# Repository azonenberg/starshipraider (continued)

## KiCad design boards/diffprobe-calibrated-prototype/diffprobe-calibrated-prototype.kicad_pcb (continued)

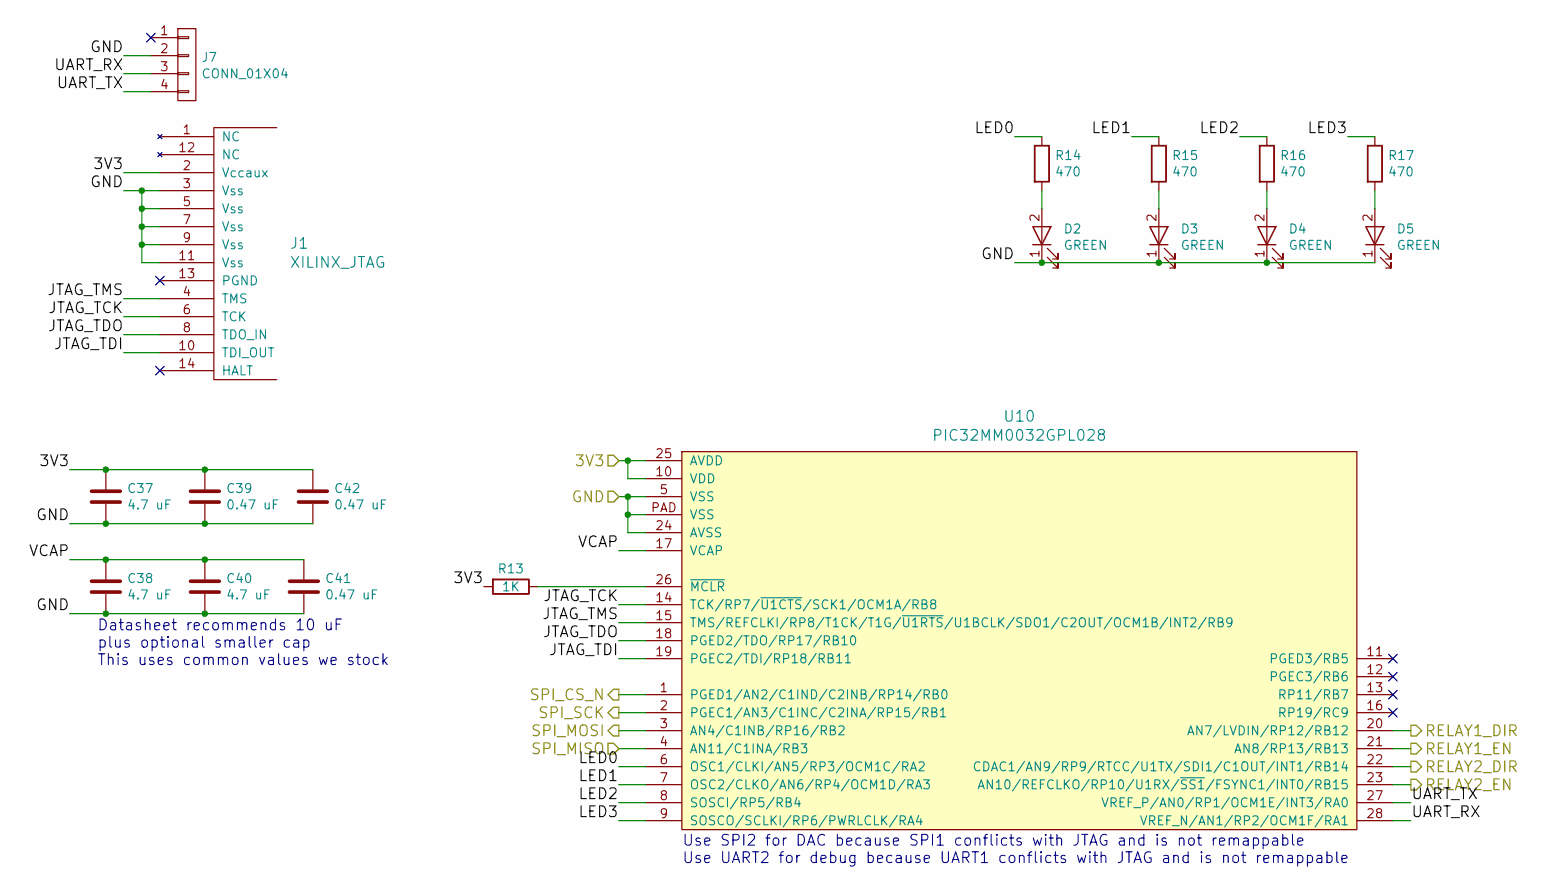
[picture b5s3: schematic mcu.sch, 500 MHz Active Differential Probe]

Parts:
C37, C38, C40: 4.7 uF; EIA_0603_CAP_NOSILK
C39, C41, C42: 0.47 uF; EIA_0402_CAP_NOSILK
D2, D3, D4, D5: GREEN; EIA_0603_LED
J1: XILINX_JTAG; XILINX_JTAG_PTH_MOLEX_0878311420
J7: CONN_01X04; CONN_HEADER_2.54MM_1x4
R13: 1K; EIA_0402_RES_NOSILK
R14, R15, R16, R17: 470; EIA_0402_RES_NOSILK
U10: PIC32MM0032GPL028; QFN_28_0.65MM_6x6MM

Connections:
/3V3: C37.1, C39.1, C42.1, J1.2 (Vccaux), R13.2, U10.10 (VDD), U10.25 (AVDD); also elsewhere on the board
/GND: C37.2, C38.2, C39.2, C40.2, C41.2, C42.2, D2.1 (K), D3.1 (K), D4.1 (K), D5.1 (K), J1.3 (Vss), J1.5 (Vss), J1.7 (Vss), J1.9 (Vss), J1.11 (Vss), J7.2, U10.5 (VSS), U10.24 (AVSS), U10.PAD (VSS); also elsewhere on the board
/Microcontroller/JTAG_TCK: J1.6 (TCK), U10.14 (TCK/RP7/~U1CTS~/SCK1/OCM1A/RB8)
/Microcontroller/JTAG_TDI: J1.10 (TDI_OUT), U10.19 (PGEC2/TDI/RP18/RB11)
/Microcontroller/JTAG_TDO: J1.8 (TDO_IN), U10.18 (PGED2/TDO/RP17/RB10)
/Microcontroller/JTAG_TMS: J1.4 (TMS), U10.15 (TMS/REFCLKI/RP8/T1CK/T1G/~U1RTS~/U1BCLK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)
/Microcontroller/LED0: R14.1, U10.6 (OSC1/CLKI/AN5/RP3/OCM1C/RA2)
/Microcontroller/LED1: R15.1, U10.7 (OSC2/CLKO/AN6/RP4/OCM1D/RA3)
/Microcontroller/LED2: R16.1, U10.8 (SOSCI/RP5/RB4)
/Microcontroller/LED3: R17.1, U10.9 (SOSCO/SCLKI/RP6/PWRLCLK/RA4)
/Microcontroller/RELAY1_DIR: U10.20 (AN7/LVDIN/RP12/RB12); also elsewhere on the board
/Microcontroller/RELAY1_EN: U10.21 (AN8/RP13/RB13); also elsewhere on the board
/Microcontroller/RELAY2_DIR: U10.22 (CDAC1/AN9/RP9/RTCC/U1TX/SDI1/C1OUT/INT1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); also elsewhere on the board
/Microcontroller/RELAY2_EN: U10.23 (AN10/REFCLKO/RP10/U1RX/~SS1~/FSYNC1/INT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); also elsewhere on the board
/Microcontroller/SPI_CS_N: U10.1 (PGED1/AN2/C1IND/C2INB/RP14/RB0); also elsewhere on the board
/Microcontroller/SPI_MISO: U10.4 (AN11/C1INA/RB3); also elsewhere on the board
/Microcontroller/SPI_MOSI: U10.3 (AN4/C1INB/RP16/RB2); also elsewhere on the board
/Microcontroller/SPI_SCK: U10.2 (PGEC1/AN3/C1INC/C2INA/RP15/RB1); also elsewhere on the board
/Microcontroller/UART_RX: J7.3, U10.28 (VREF_N/AN1/RP2/OCM1F/RA1)
/Microcontroller/UART_TX: J7.4, U10.27 (VREF_P/AN0/RP1/OCM1E/INT3/RA0)
/Microcontroller/VCAP: C38.1, C40.1, C41.1, U10.17 (VCAP)
unnamed: D2.2 (A), R14.2
unnamed: D3.2 (A), R15.2
unnamed: D4.2 (A), R16.2
unnamed: D5.2 (A), R17.2
unnamed: R13.1, U10.26 (~MCLR)

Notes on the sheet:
Use SPI2 for DAC because SPI1 conflicts with JTAG and is not remappable Use UART2 for debug because UART1 conflicts with JTAG and is not remappable
Datasheet recommends 10 uF plus optional smaller cap This uses common values we stock

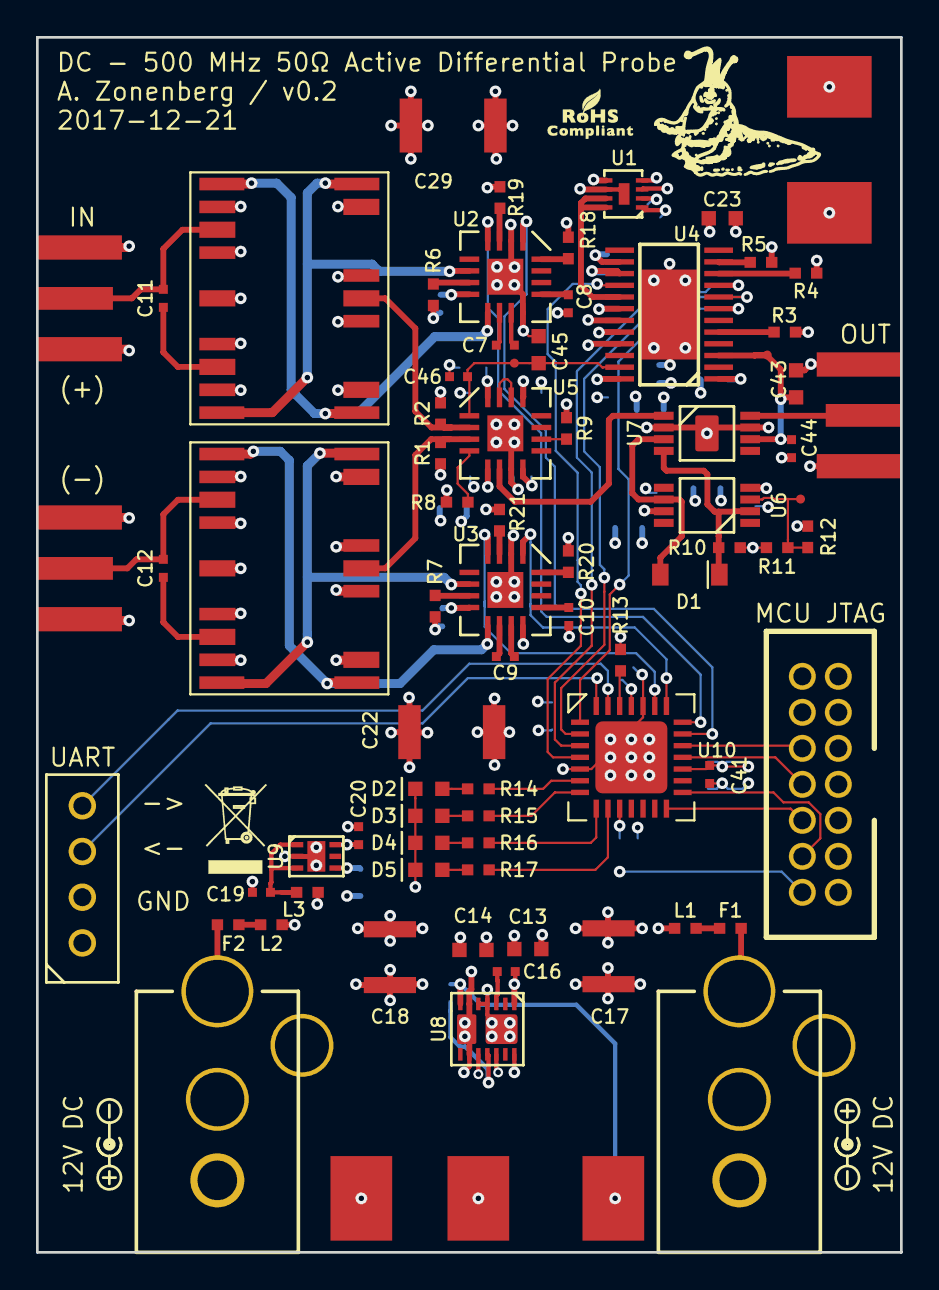
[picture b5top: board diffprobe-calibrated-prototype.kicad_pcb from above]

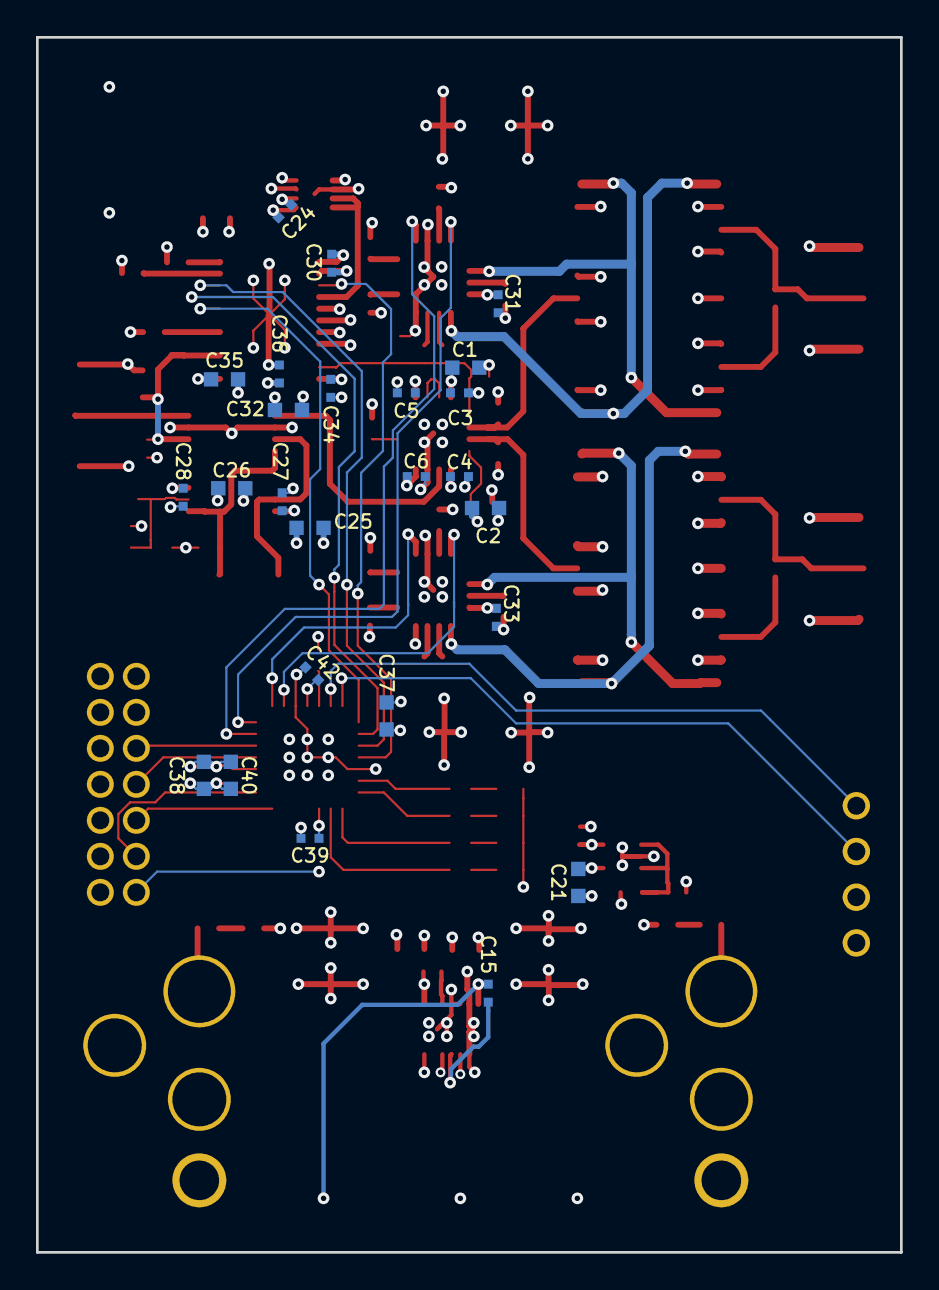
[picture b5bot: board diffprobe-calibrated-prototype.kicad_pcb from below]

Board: 4 copper layers, 48.0 x 67.5 mm, 104 parts (25 on the bottom side), 74 nets.

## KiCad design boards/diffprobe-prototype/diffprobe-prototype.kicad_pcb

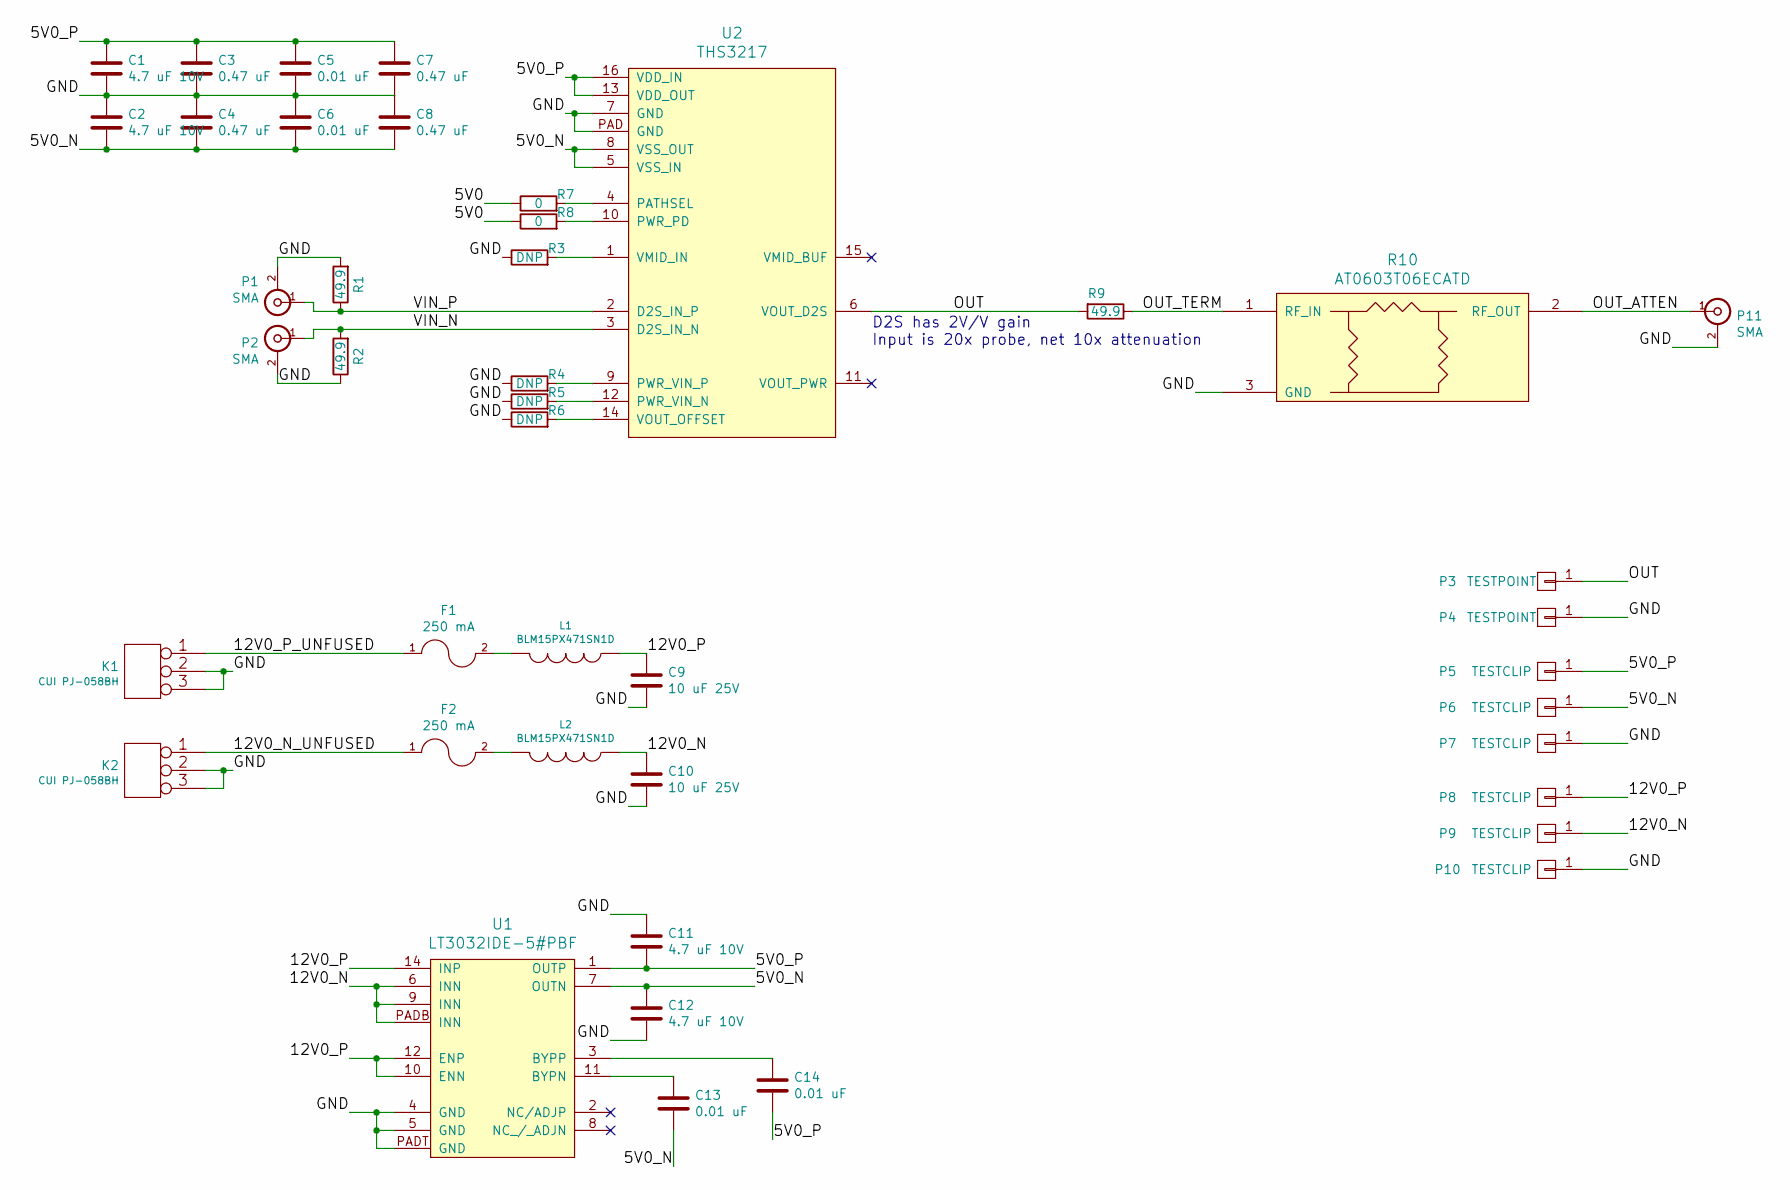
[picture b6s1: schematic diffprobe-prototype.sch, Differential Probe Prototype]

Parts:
C1, C2, C11, C12: 4.7 uF 10V; EIA_0805_CAP_NOSILK
C3, C4, C7, C8: 0.47 uF; EIA_0402_CAP_NOSILK
C5, C6, C13, C14: 0.01 uF; EIA_0402_CAP_NOSILK
C9, C10: 10 uF 25V; EIA_1210_CAP_NOSILK
F1, F2: 250 mA; EIA_0402_RES_NOSILK
K1, K2: CUI PJ-058BH; CONN_CUI_PJ-058BH_HIPWR_BARREL_NOSLOT
L1, L2: BLM15PX471SN1D; EIA_0402_RES_NOSILK
P1, P2, P11: SMA; CONN_SMA_EDGE_SAMTEC_SMA_J_P_H_ST_EM1
P3, P4: TESTPOINT; TESTPOINT_BARETRACE_328UM
P5, P6, P7, P8, P9, P10: TESTCLIP; TESTPOINT_SMT_KEYSTONE_5016
R1, R2, R9: 49.9; EIA_0402_RES_NOSILK
R3, R4, R5, R6: DNP; EIA_0402_RES_NOSILK
R7, R8: 0; EIA_0402_RES_NOSILK
R10: AT0603T06ECATD
U1: LT3032IDE-5#PBF
U2: THS3217

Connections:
/5V0_N: C2.2, C4.2, C6.2, C8.2, C12.1, C13.2, P6.1, U1.7 (OUTN), U2.5 (VSS_IN), U2.8 (VSS_OUT)
/12V0_N: C10.1, L2.1, P9.1, U1.6 (INN), U1.9 (INN), U1.PADB (INN)
/12V0_N_UNFUSED: F2.1, K2.1
/12V0_P: C9.1, L1.1, P8.1, U1.10 (ENN), U1.12 (ENP), U1.14 (INP)
/12V0_P_UNFUSED: F1.1, K1.1
/GND: C1.2, C2.1, C3.2, C4.1, C5.2, C6.1, C7.2, C8.1, C9.2, C10.2, C11.1, C12.2, K1.2 (PM), K1.3, K2.2 (PM), K2.3, P1.2 (Ext), P2.2 (Ext), P4.1, P7.1, P10.1, P11.2 (Ext), R1.2, R2.1, R3.1, R4.1, R5.1, R6.1, R10.3 (GND), U1.4 (GND), U1.5 (GND), U1.PADT (GND), U2.7 (GND), U2.PAD (GND)
/OUT: P3.1, R9.2, U2.6 (VOUT_D2S)
/OUT_ATTEN: P11.1 (In), R10.2 (RF_OUT)
/OUT_TERM: R9.1, R10.1 (RF_IN)
/VIN_N: P2.1 (In), R2.2, U2.3 (D2S_IN_N)
/VIN_P: P1.1 (In), R1.1, U2.2 (D2S_IN_P)
unnamed: C13.1, U1.11 (BYPN)
unnamed: C14.1, U1.3 (BYPP)
unnamed: F1.2, L1.2
unnamed: F2.2, L2.2
unnamed: R3.2, U2.1 (VMID_IN)
unnamed: R4.2, U2.9 (PWR_VIN_P)
unnamed: R5.2, U2.12 (PWR_VIN_N)
unnamed: R6.2, U2.14 (VOUT_OFFSET)
unnamed: R7.2, U2.4 (PATHSEL)
unnamed: R8.2, U2.10 (PWR_PD)

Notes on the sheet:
D2S has 2V/V gain Input is 20x probe, net 10x attenuation

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
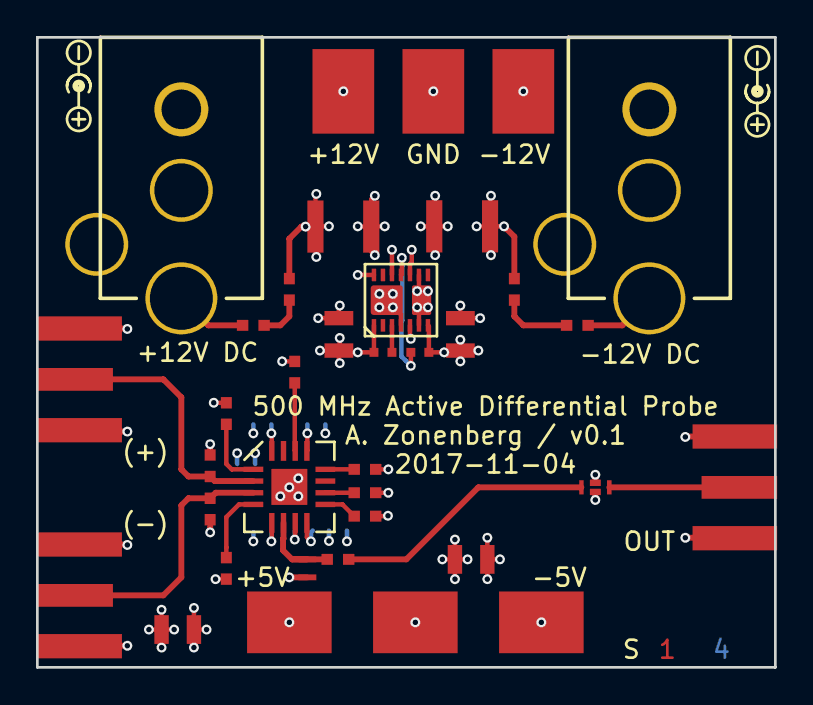
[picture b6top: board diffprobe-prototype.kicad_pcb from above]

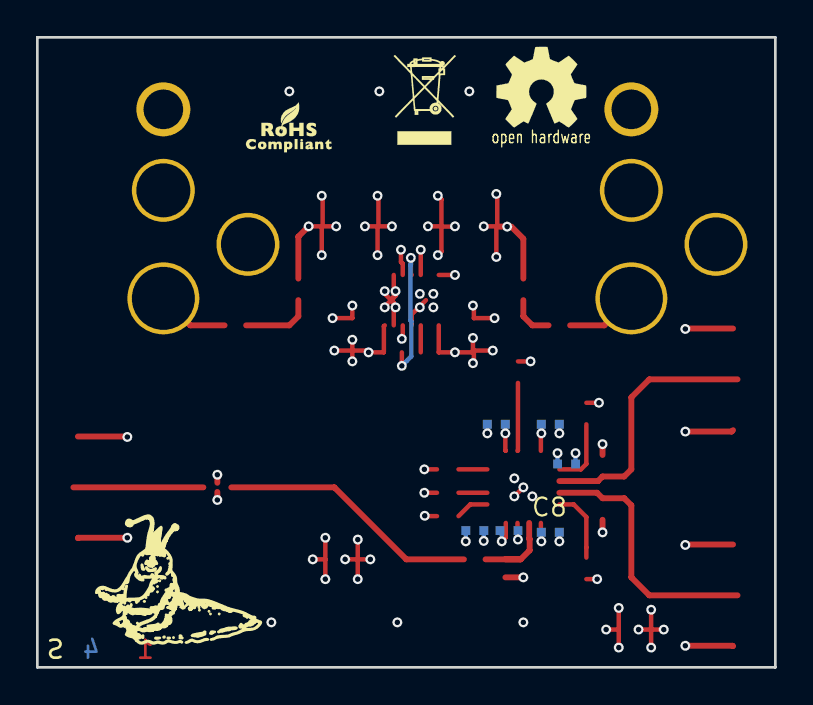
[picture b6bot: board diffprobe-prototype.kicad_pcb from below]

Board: 4 copper layers, 41.0 x 35.0 mm, 43 parts (6 on the bottom side), 22 nets.

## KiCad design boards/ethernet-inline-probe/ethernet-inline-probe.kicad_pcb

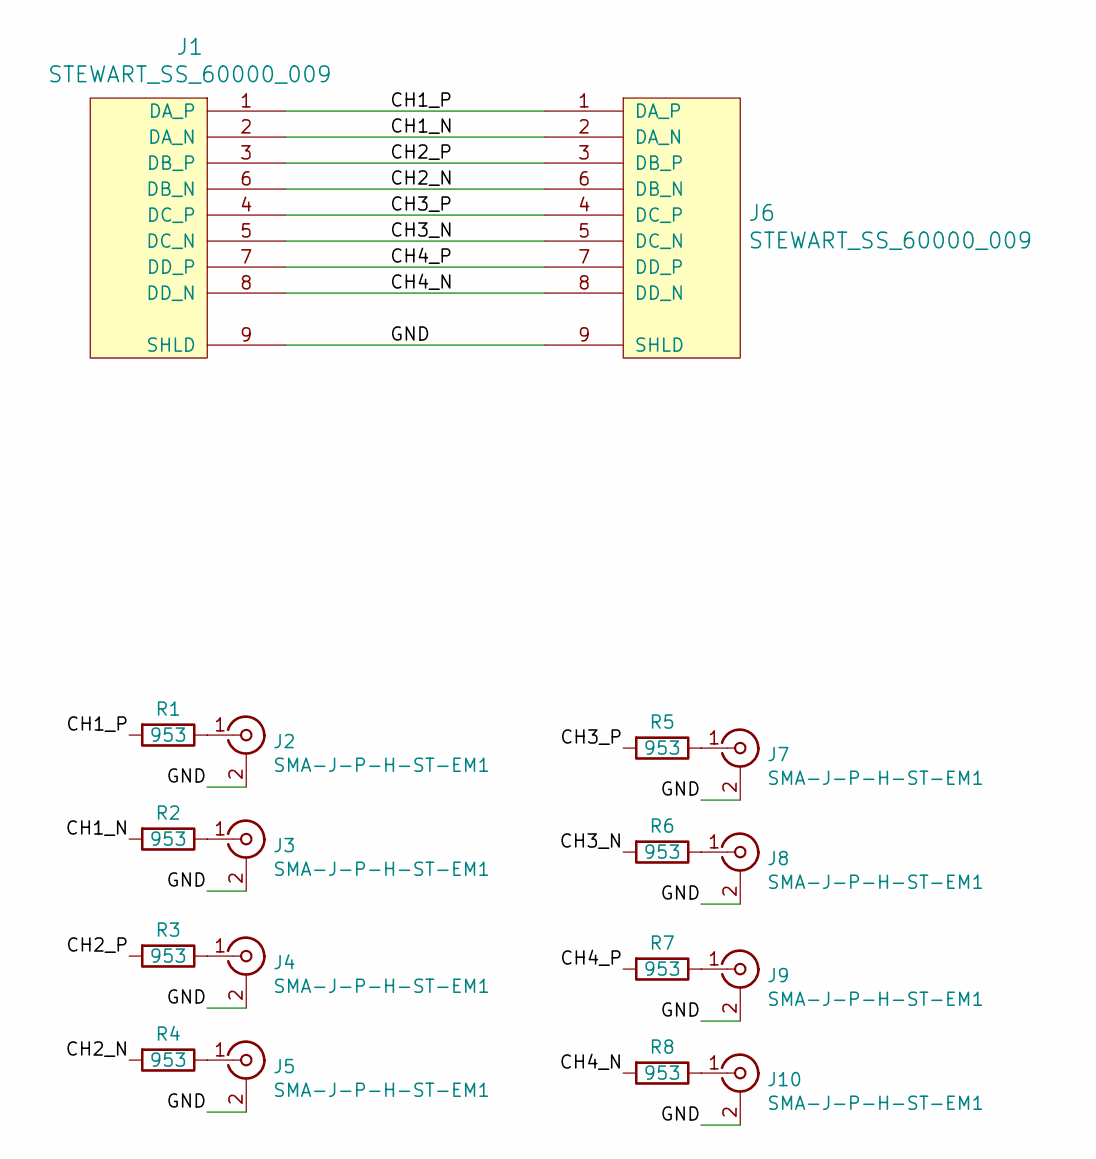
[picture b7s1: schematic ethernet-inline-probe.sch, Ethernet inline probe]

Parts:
J1, J6: STEWART_SS_60000_009; CONN_STEWART_SS60000_009
J2, J3, J4, J5, J7, J8, J9, J10: SMA-J-P-H-ST-EM1; CONN_SMA_EDGE_SAMTEC_SMA_J_P_H_ST_EM1
R1, R2, R3, R4, R5, R6, R7, R8: 953; EIA_0402_RES_NOSILK

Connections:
/CH1_N: J1.2 (DA_N), J6.2 (DA_N), R2.2
/CH1_P: J1.1 (DA_P), J6.1 (DA_P), R1.2
/CH2_N: J1.6 (DB_N), J6.6 (DB_N), R4.2
/CH2_P: J1.3 (DB_P), J6.3 (DB_P), R3.2
/CH3_N: J1.5 (DC_N), J6.5 (DC_N), R6.2
/CH3_P: J1.4 (DC_P), J6.4 (DC_P), R5.2
/CH4_N: J1.8 (DD_N), J6.8 (DD_N), R8.2
/CH4_P: J1.7 (DD_P), J6.7 (DD_P), R7.2
/GND: J1.9 (SHLD), J2.2 (Ext), J3.2 (Ext), J4.2 (Ext), J5.2 (Ext), J6.9 (SHLD), J7.2 (Ext), J8.2 (Ext), J9.2 (Ext), J10.2 (Ext)
unnamed: J2.1 (In), R1.1
unnamed: J3.1 (In), R2.1
unnamed: J4.1 (In), R3.1
unnamed: J5.1 (In), R4.1
unnamed: J7.1 (In), R5.1
unnamed: J8.1 (In), R6.1
unnamed: J9.1 (In), R7.1
unnamed: J10.1 (In), R8.1

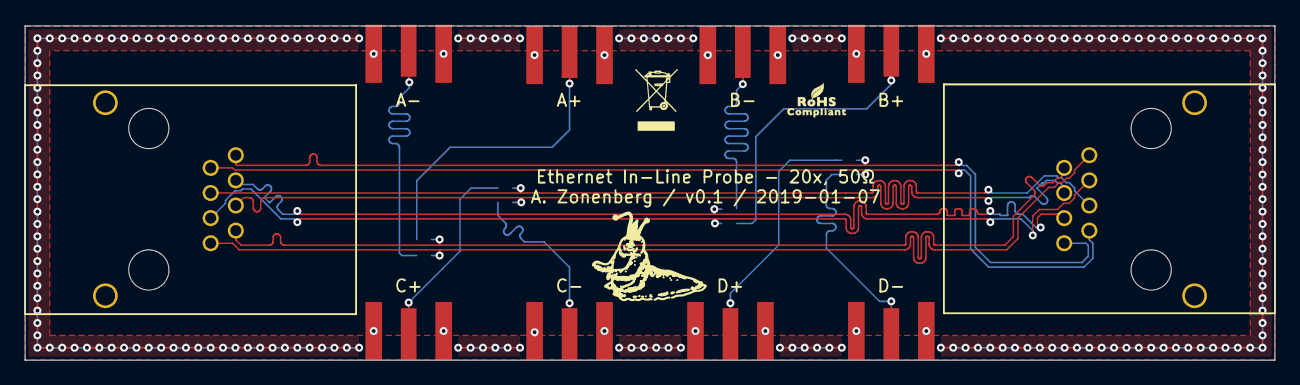
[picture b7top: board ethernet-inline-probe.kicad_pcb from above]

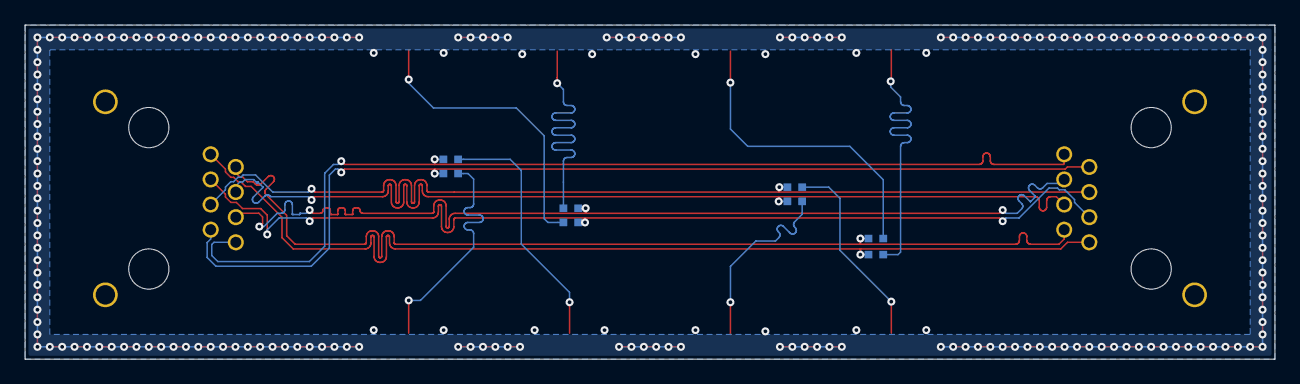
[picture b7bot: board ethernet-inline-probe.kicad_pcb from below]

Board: 4 copper layers, 101.0 x 27.0 mm, 18 parts (8 on the bottom side), 17 nets.
